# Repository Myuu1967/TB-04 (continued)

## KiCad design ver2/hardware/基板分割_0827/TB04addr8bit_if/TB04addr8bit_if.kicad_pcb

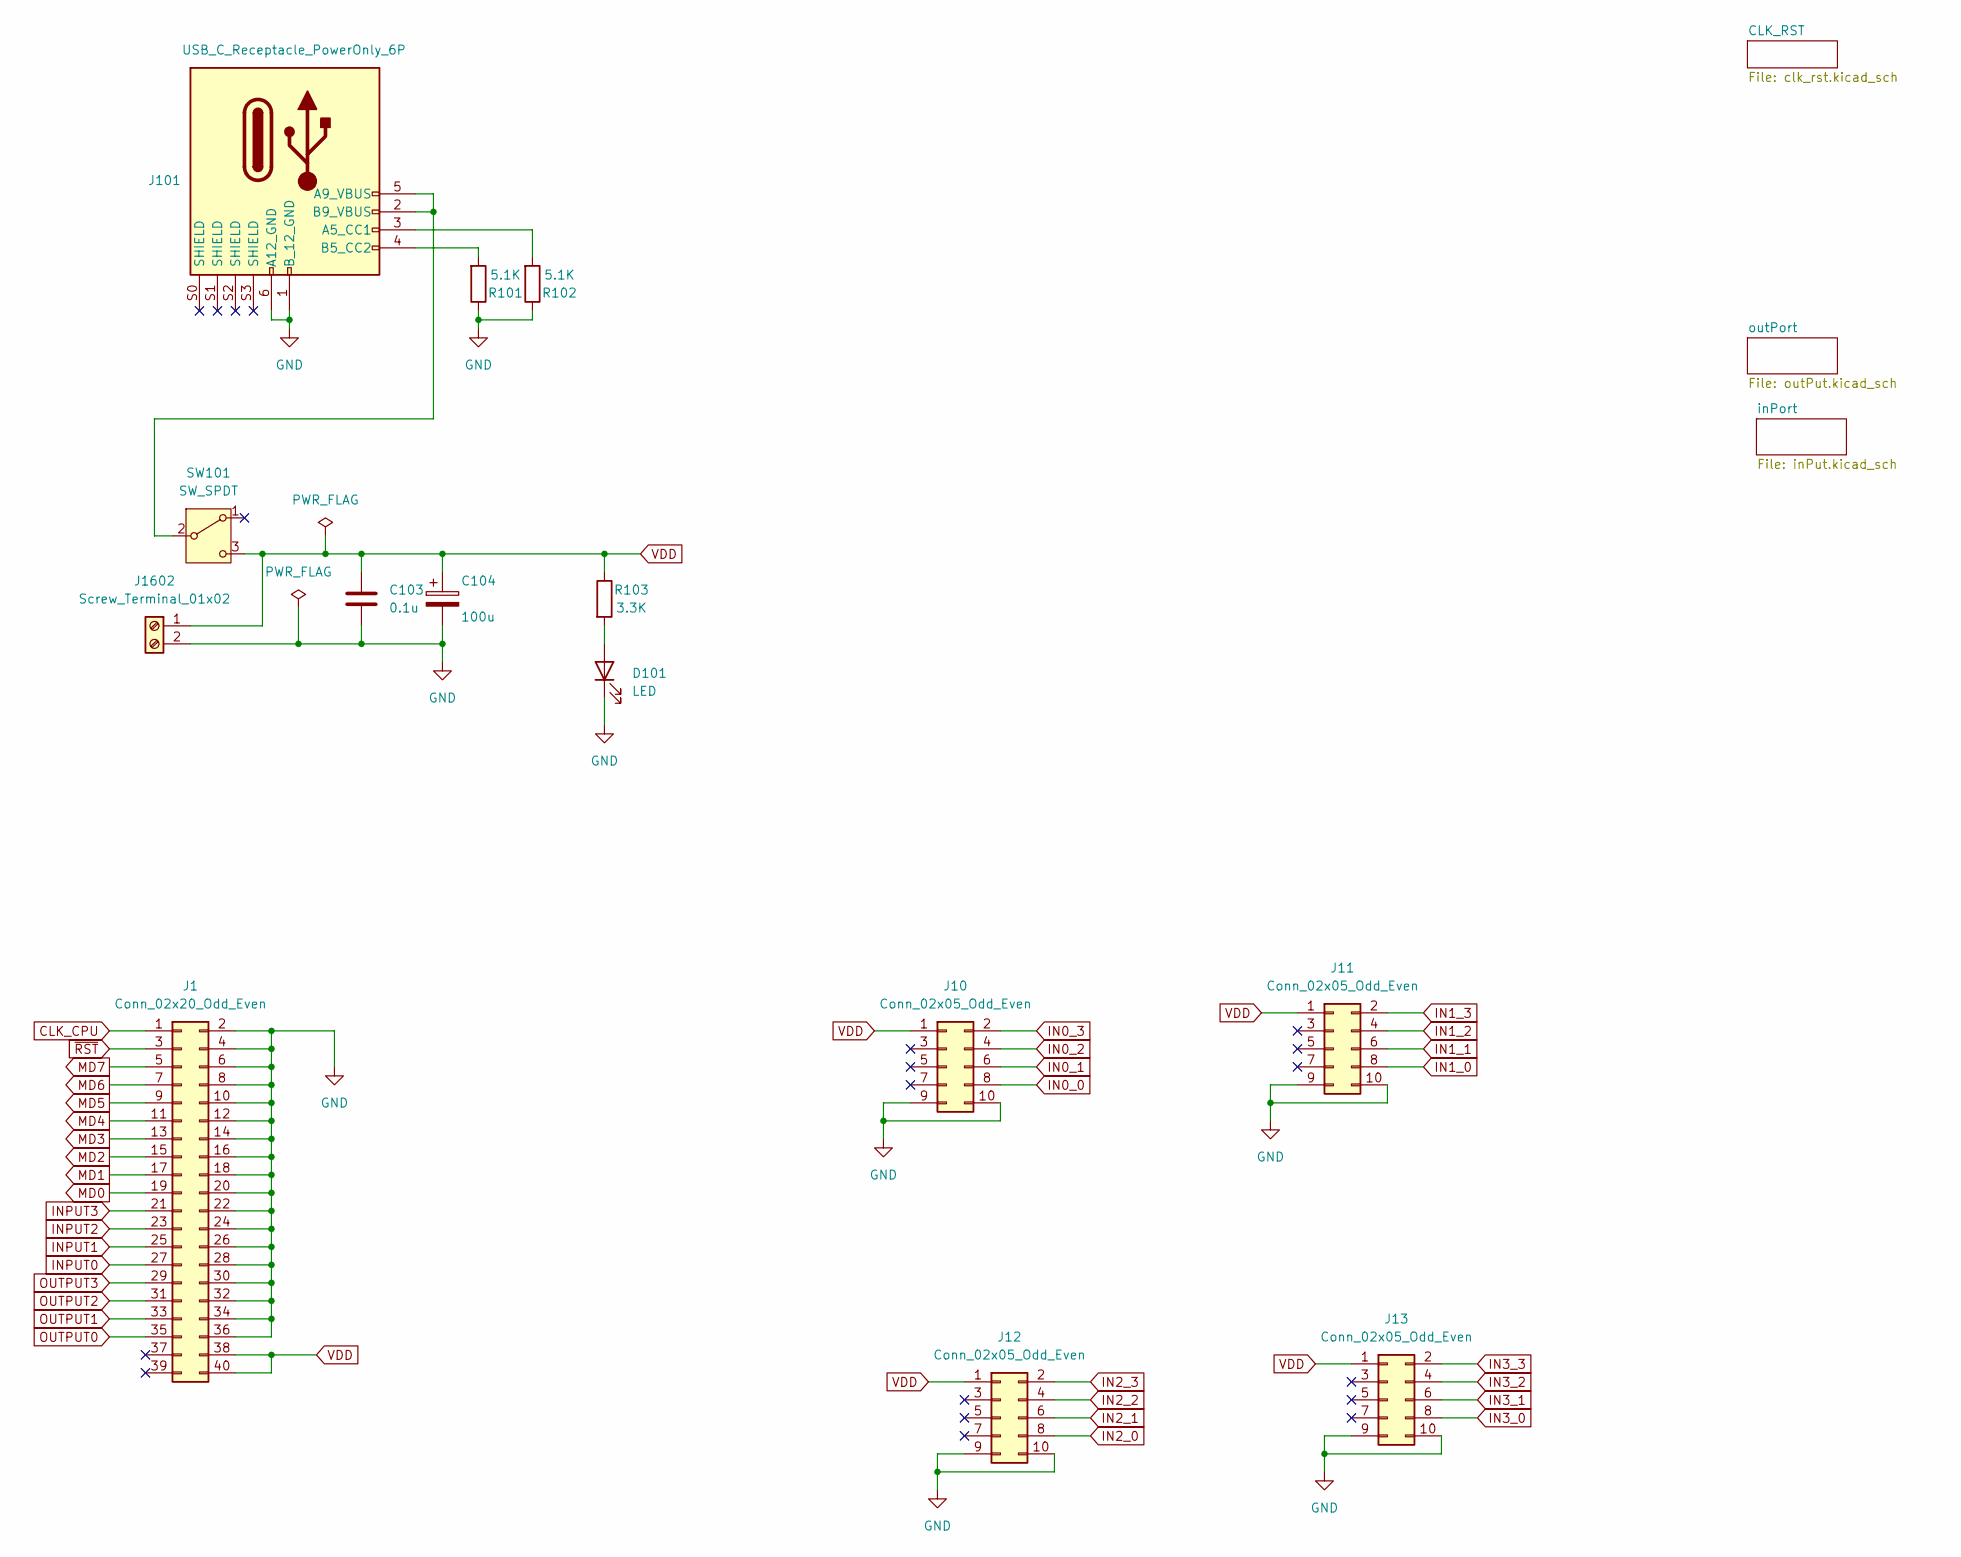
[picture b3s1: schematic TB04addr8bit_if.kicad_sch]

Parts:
C103: 0.1u; C_Disc_D4.3mm_W1.9mm_P5.00mm
C104: 100u; CP_Radial_D5.0mm_P2.00mm
D101: LED; LED_D3.0mm_Clear
J1: Conn_02x20_Odd_Even; PinSocket_2x20_P2.54mm_Vertical
J10, J11, J12, J13: Conn_02x05_Odd_Even; PinSocket_2x05_P2.54mm_Vertical
J101: USB_C_Receptacle_PowerOnly_6P; USB_C_receptacle_onlypower_tanuki
J1602: Screw_Terminal_01x02; TerminalBlock_MaiXu_MX126-5.0-02P_1x02_P5.00mm
R101, R102: 5.1K; R_Axial_DIN0207_L6.3mm_D2.5mm_P10.16mm_Horizontal
R103: 3.3K; R_Axial_DIN0207_L6.3mm_D2.5mm_P7.62mm_Horizontal
SW101: SW_SPDT; sw_slide

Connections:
CLK_CPU: J1.1; also elsewhere on the board
GND: C103.2, C104.2, D101.1 (K), J1.2, J1.4, J1.6, J1.8, J1.10, J1.12, J1.14, J1.16, J1.18, J1.20, J1.22, J1.24, J1.26, J1.28, J1.30, J1.32, J1.34, J1.36, J10.9, J10.10, J11.9, J11.10, J12.9, J12.10, J13.9, J13.10, J101.1 (B_12_GND), J101.6 (A12_GND), J1602.2, R101.1, R102.1; also elsewhere on the board
IN0_0: J10.8; also elsewhere on the board
IN0_1: J10.6; also elsewhere on the board
IN0_2: J10.4; also elsewhere on the board
IN0_3: J10.2; also elsewhere on the board
IN1_0: J11.8; also elsewhere on the board
IN1_1: J11.6; also elsewhere on the board
IN1_2: J11.4; also elsewhere on the board
IN1_3: J11.2; also elsewhere on the board
IN2_0: J12.8; also elsewhere on the board
IN2_1: J12.6; also elsewhere on the board
IN2_2: J12.4; also elsewhere on the board
IN2_3: J12.2; also elsewhere on the board
IN3_0: J13.8; also elsewhere on the board
IN3_1: J13.6; also elsewhere on the board
IN3_2: J13.4; also elsewhere on the board
IN3_3: J13.2; also elsewhere on the board
INPUT0: J1.27; also elsewhere on the board
INPUT1: J1.25; also elsewhere on the board
INPUT2: J1.23; also elsewhere on the board
INPUT3: J1.21; also elsewhere on the board
MD0: J1.19; also elsewhere on the board
MD1: J1.17; also elsewhere on the board
MD2: J1.15; also elsewhere on the board
MD3: J1.13; also elsewhere on the board
MD4: J1.11; also elsewhere on the board
MD5: J1.9; also elsewhere on the board
MD6: J1.7; also elsewhere on the board
MD7: J1.5; also elsewhere on the board
unnamed: D101.2 (A), R103.2
unnamed: J101.3 (A5_CC1), R102.2
unnamed: J101.2 (B9_VBUS), J101.5 (A9_VBUS), SW101.2 (B)
unnamed: J101.4 (B5_CC2), R101.2
OUTPUT0: J1.35; also elsewhere on the board
OUTPUT1: J1.33; also elsewhere on the board
OUTPUT2: J1.31; also elsewhere on the board
OUTPUT3: J1.29; also elsewhere on the board
VDD: C103.1, C104.1, J1.38, J1.40, J10.1, J11.1, J12.1, J13.1, J1602.1, R103.1, SW101.3 (C); also elsewhere on the board
~RST: J1.3; also elsewhere on the board

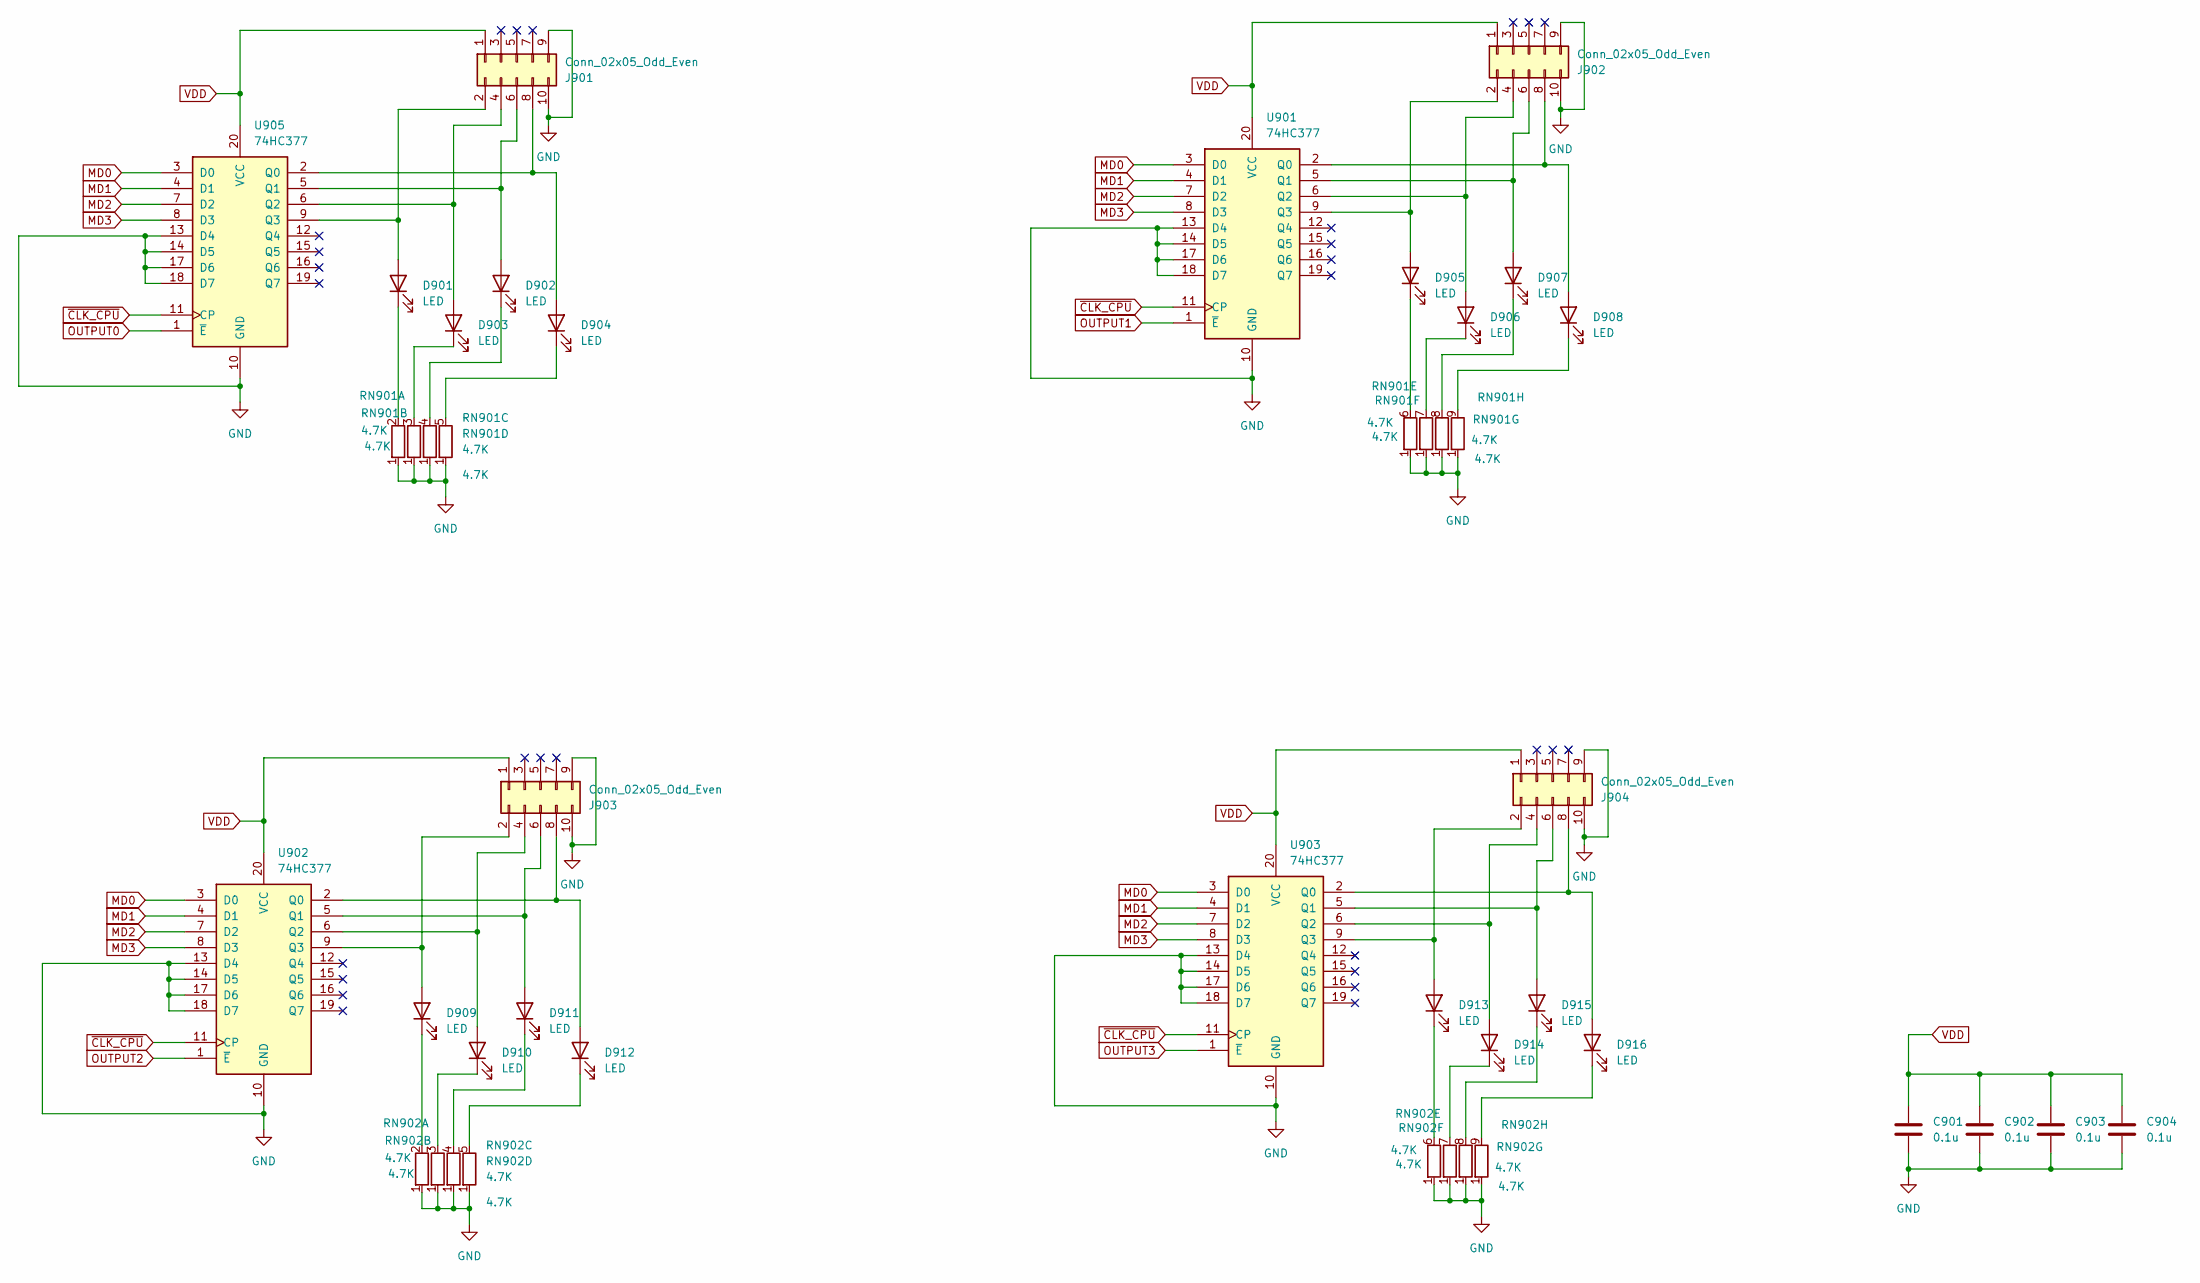
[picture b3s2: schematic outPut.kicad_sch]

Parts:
C901, C902, C903, C904: 0.1u; C_Disc_D4.3mm_W1.9mm_P5.00mm
D901, D902, D903, D904, D905, D906, D907, D908, D909, D910, D911, D912, D913, D914, D915, D916: LED; LED_D3.0mm_Clear
J901, J902, J903, J904: Conn_02x05_Odd_Even; PinSocket_2x05_P2.54mm_Vertical
RN901, RN902: 4.7K; R_Array_SIP9
U901, U902, U903, U905: 74HC377; DIP-20_W7.62mm_Socket

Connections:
GND: C901.1, C902.1, C903.1, C904.1, J901.9, J901.10, J902.9, J902.10, J903.9, J903.10, J904.9, J904.10, RN901.1 (R1), RN902.1 (R1), U901.10 (GND), U901.13 (D4), U901.14 (D5), U901.17 (D6), U901.18 (D7), U902.10 (GND), U902.13 (D4), U902.14 (D5), U902.17 (D6), U902.18 (D7), U903.10 (GND), U903.13 (D4), U903.14 (D5), U903.17 (D6), U903.18 (D7), U905.10 (GND), U905.13 (D4), U905.14 (D5), U905.17 (D6), U905.18 (D7); also elsewhere on the board
MD0: U901.3 (D0), U902.3 (D0), U903.3 (D0), U905.3 (D0); also elsewhere on the board
MD1: U901.4 (D1), U902.4 (D1), U903.4 (D1), U905.4 (D1); also elsewhere on the board
MD2: U901.7 (D2), U902.7 (D2), U903.7 (D2), U905.7 (D2); also elsewhere on the board
MD3: U901.8 (D3), U902.8 (D3), U903.8 (D3), U905.8 (D3); also elsewhere on the board
unnamed: D901.2 (A), J901.2, U905.9 (Q3)
unnamed: D901.1 (K), RN901.2 (R1.2)
unnamed: D902.2 (A), J901.6, U905.5 (Q1)
unnamed: D902.1 (K), RN901.4 (R3.2)
unnamed: D903.2 (A), J901.4, U905.6 (Q2)
unnamed: D903.1 (K), RN901.3 (R2.2)
unnamed: D904.2 (A), J901.8, U905.2 (Q0)
unnamed: D904.1 (K), RN901.5 (R4.2)
unnamed: D905.2 (A), J902.2, U901.9 (Q3)
unnamed: D905.1 (K), RN901.6 (R5.2)
unnamed: D906.2 (A), J902.4, U901.6 (Q2)
unnamed: D906.1 (K), RN901.7 (R6.2)
unnamed: D907.2 (A), J902.6, U901.5 (Q1)
unnamed: D907.1 (K), RN901.8 (R7.2)
unnamed: D908.2 (A), J902.8, U901.2 (Q0)
unnamed: D908.1 (K), RN901.9 (R8.2)
unnamed: D909.2 (A), J903.2, U902.9 (Q3)
unnamed: D909.1 (K), RN902.2 (R1.2)
unnamed: D910.2 (A), J903.4, U902.6 (Q2)
unnamed: D910.1 (K), RN902.3 (R2.2)
unnamed: D911.2 (A), J903.6, U902.5 (Q1)
unnamed: D911.1 (K), RN902.4 (R3.2)
unnamed: D912.2 (A), J903.8, U902.2 (Q0)
unnamed: D912.1 (K), RN902.5 (R4.2)
unnamed: D913.2 (A), J904.2, U903.9 (Q3)
unnamed: D913.1 (K), RN902.6 (R5.2)
unnamed: D914.2 (A), J904.4, U903.6 (Q2)
unnamed: D914.1 (K), RN902.7 (R6.2)
unnamed: D915.2 (A), J904.6, U903.5 (Q1)
unnamed: D915.1 (K), RN902.8 (R7.2)
unnamed: D916.2 (A), J904.8, U903.2 (Q0)
unnamed: D916.1 (K), RN902.9 (R8.2)
OUTPUT0: U905.1 (~E); also elsewhere on the board
OUTPUT1: U901.1 (~E); also elsewhere on the board
OUTPUT2: U902.1 (~E); also elsewhere on the board
OUTPUT3: U903.1 (~E); also elsewhere on the board
VDD: C901.2, C902.2, C903.2, C904.2, J901.1, J902.1, J903.1, J904.1, U901.20 (VCC), U902.20 (VCC), U903.20 (VCC), U905.20 (VCC); also elsewhere on the board
~CLK_CPU: U901.11 (CP), U902.11 (CP), U903.11 (CP), U905.11 (CP); also elsewhere on the board

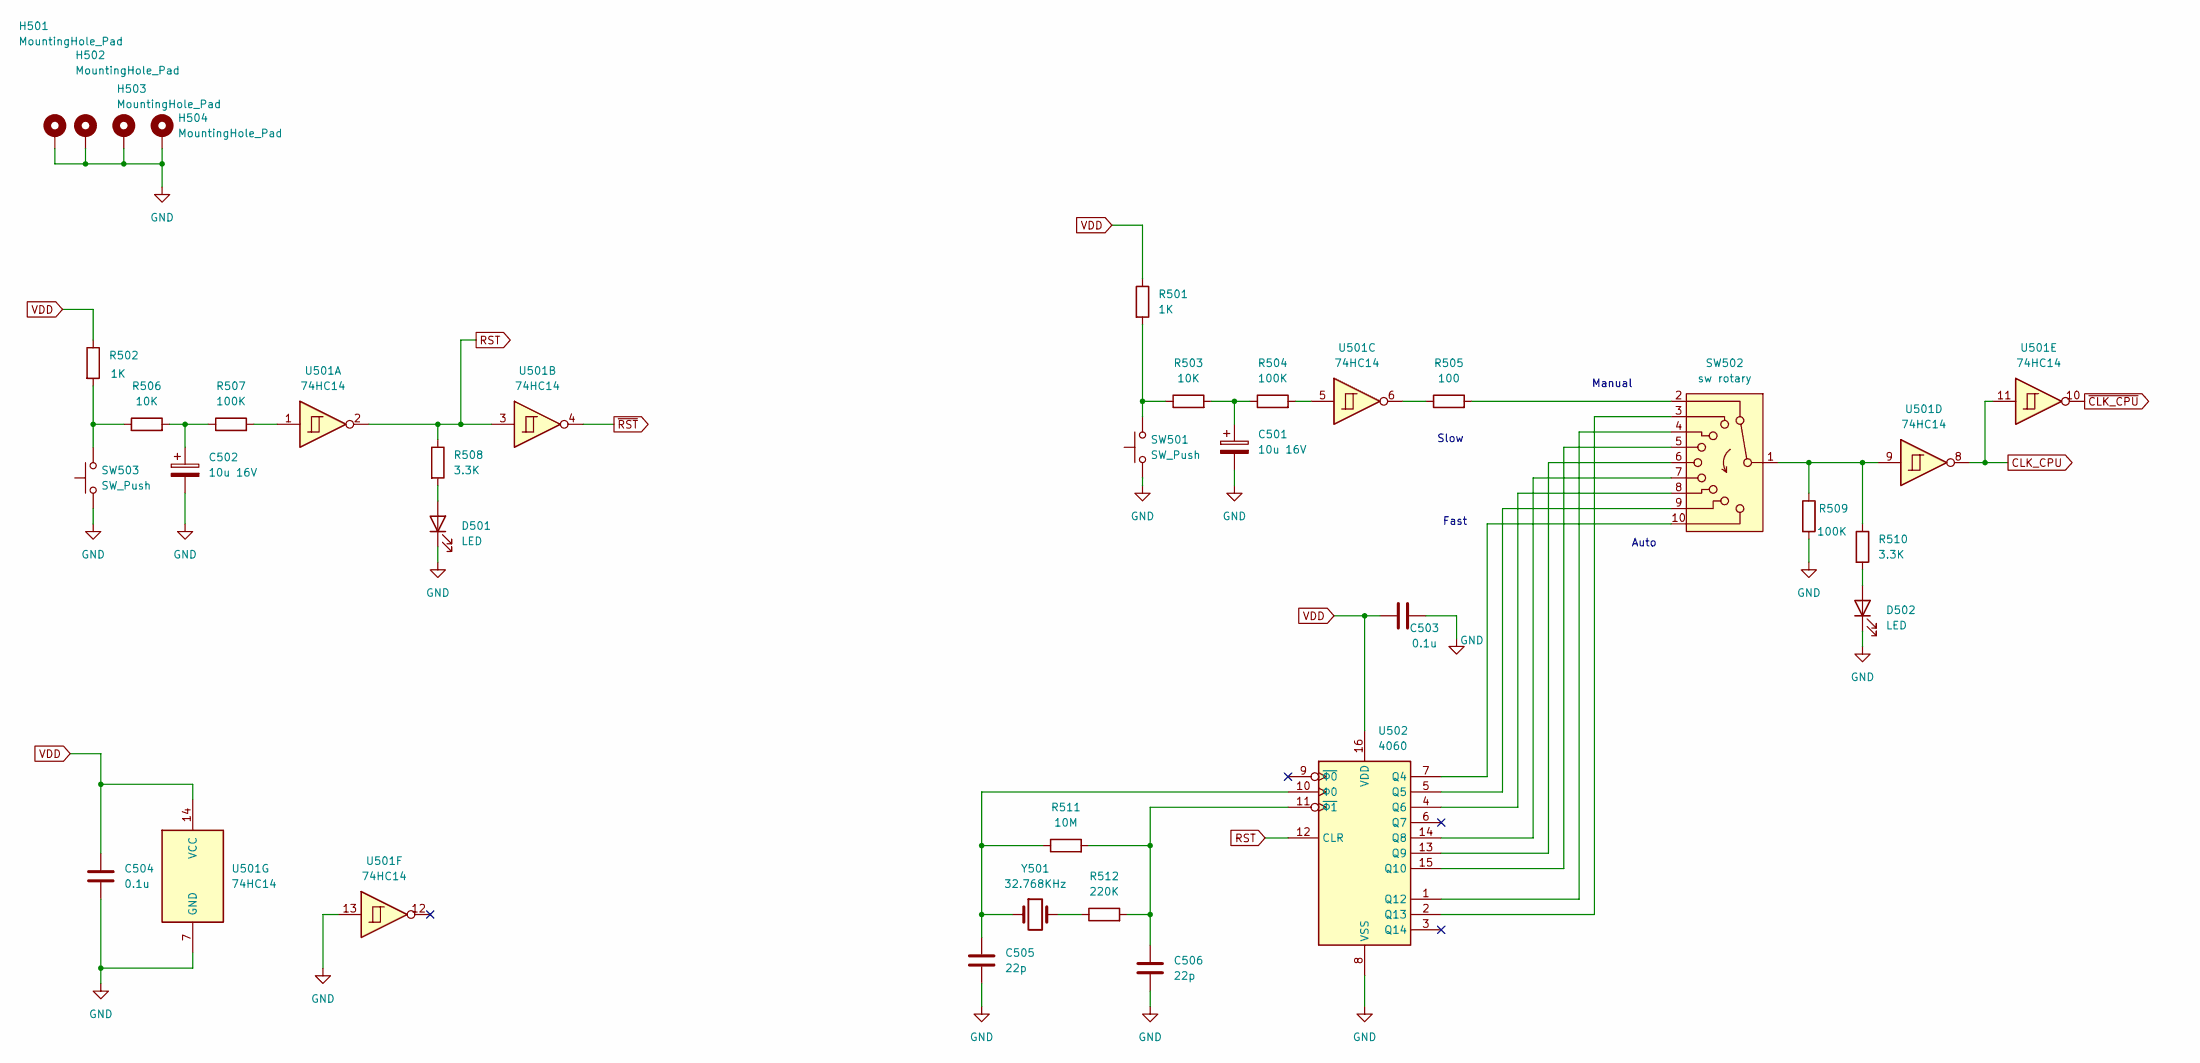
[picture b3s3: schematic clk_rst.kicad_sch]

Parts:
C501, C502: 10u 16V; CP_Radial_D5.0mm_P2.00mm
C503, C504: 0.1u; C_Disc_D4.3mm_W1.9mm_P5.00mm
C505, C506: 22p; C_Disc_D4.3mm_W1.9mm_P5.00mm
D501, D502: LED; LED_D3.0mm_Clear
H501, H502, H503, H504: MountingHole_Pad; MountingHole_3.2mm_M3_Pad_Via
R501, R502: 1K; R_Axial_DIN0207_L6.3mm_D2.5mm_P10.16mm_Horizontal
R503, R506: 10K; R_Axial_DIN0207_L6.3mm_D2.5mm_P10.16mm_Horizontal
R504, R507, R509: 100K; R_Axial_DIN0207_L6.3mm_D2.5mm_P7.62mm_Horizontal
R505: 100; R_Axial_DIN0207_L6.3mm_D2.5mm_P10.16mm_Horizontal
R508, R510: 3.3K; R_Axial_DIN0207_L6.3mm_D2.5mm_P7.62mm_Horizontal
R511: 10M; R_Axial_DIN0207_L6.3mm_D2.5mm_P10.16mm_Horizontal
R512: 220K; R_Axial_DIN0207_L6.3mm_D2.5mm_P10.16mm_Horizontal
SW501, SW503: SW_Push; SW_Tactile_Straight_KSL0Axx1LFTR
SW502: sw rotary; SW_Rotary_1x9_Alpha_SR1712F-0109
U501: 74HC14; DIP-14_W7.62mm_Socket
U502: 4060; DIP-16_W7.62mm_Socket
Y501: 32.768KHz; PinSocket_1x02_P2.00mm_Vertical

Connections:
CLK_CPU: U501.8, U501.11; also elsewhere on the board
GND: C501.2, C502.2, C503.1, C504.2, C505.2, C506.2, D501.1 (K), D502.1 (K), H501.1 (1_1), H502.1 (1_1), H503.1 (1_1), H504.1 (1_1), R509.2, SW501.1, SW503.1, U501.7 (GND), U501.13, U502.8 (VSS); also elsewhere on the board
unnamed: C501.1, R503.2, R504.1
unnamed: C502.1, R506.2, R507.1
unnamed: D501.2 (A), R508.2
unnamed: D502.2 (A), R510.2
unnamed: R501.2, R503.1, SW501.2
unnamed: R502.2, R506.1, SW503.2
unnamed: R504.2, U501.5
unnamed: R505.1, U501.6
unnamed: R505.2, SW502.2
unnamed: R507.2, U501.1
unnamed: R509.1, R510.1, SW502.1, U501.9
unnamed: R512.1, Y501.2
unnamed: SW502.10, U502.7 (Q4)
unnamed: SW502.9, U502.5 (Q5)
unnamed: SW502.8, U502.4 (Q6)
unnamed: SW502.7, U502.14 (Q8)
unnamed: SW502.6, U502.13 (Q9)
unnamed: SW502.5, U502.15 (Q10)
unnamed: SW502.4, U502.1 (Q12)
unnamed: SW502.3, U502.2 (Q13)
unnamed: C506.1, R511.2, R512.2, U502.11 (~Φ1)
unnamed: C505.1, R511.1, U502.10 (Φ0), Y501.1
RST: R508.1, U501.2, U501.3, U502.12 (CLR)
VDD: C503.2, C504.1, R501.1, R502.1, U501.14 (VCC), U502.16 (VDD); also elsewhere on the board
~CLK_CPU: U501.10; also elsewhere on the board
~RST: U501.4; also elsewhere on the board

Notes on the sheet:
Auto
Manual
Slow
Fast

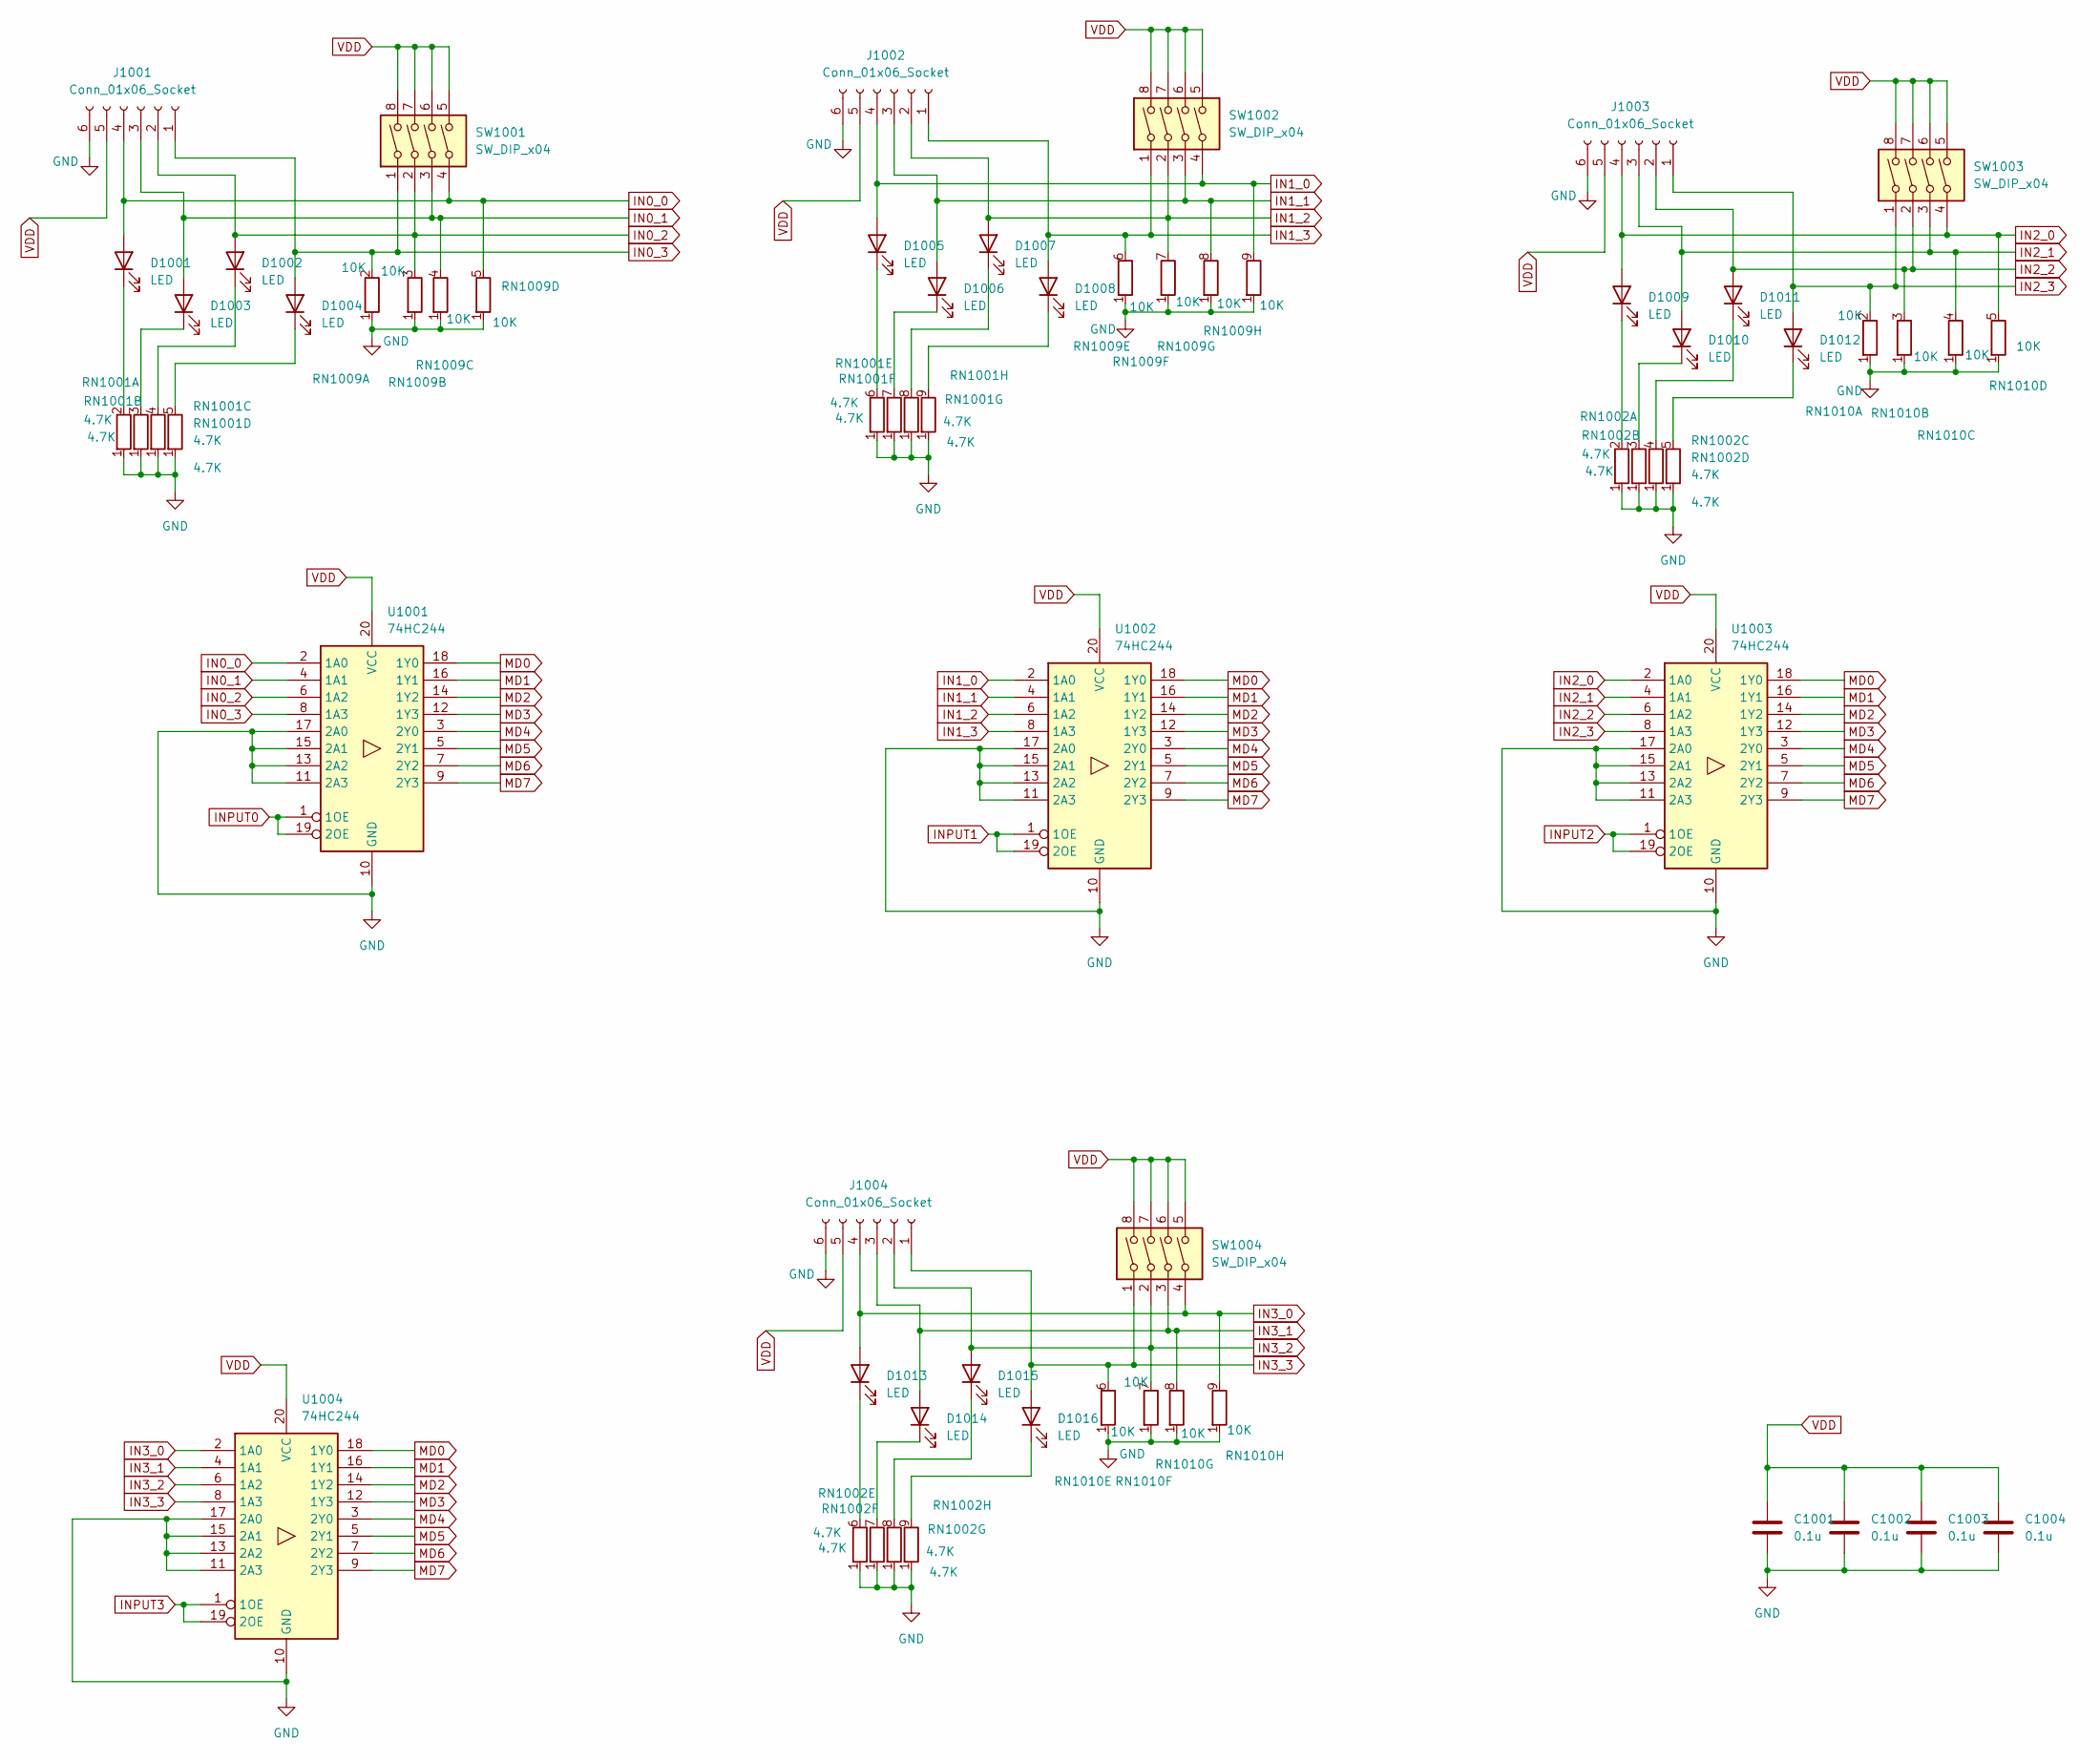
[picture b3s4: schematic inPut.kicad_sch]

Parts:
C1001, C1002, C1003, C1004: 0.1u; C_Disc_D4.3mm_W1.9mm_P5.00mm
D1001, D1002, D1003, D1004, D1005, D1006, D1007, D1008, D1009, D1010, D1011, D1012, D1013, D1014, D1015, D1016: LED; LED_D3.0mm_Clear
J1001, J1002, J1003, J1004: Conn_01x06_Socket; PinSocket_1x06_P2.54mm_Vertical
RN1001, RN1002: 4.7K; R_Array_SIP9
RN1009, RN1010: 10K; R_Array_SIP9
SW1001, SW1002, SW1003, SW1004: SW_DIP_x04; SW_DIP_SPSTx04_Slide_9.78x12.34mm_W7.62mm_P2.54mm
U1001, U1002, U1003, U1004: 74HC244; DIP-20_W7.62mm_Socket

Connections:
GND: C1001.1, C1002.1, C1003.1, C1004.1, J1001.6, J1002.6, J1003.6, J1004.6, RN1001.1 (R1), RN1002.1 (R1), RN1009.1 (R1), RN1010.1 (R1), U1001.10 (GND), U1001.11 (2A3), U1001.13 (2A2), U1001.15 (2A1), U1001.17 (2A0), U1002.10 (GND), U1002.11 (2A3), U1002.13 (2A2), U1002.15 (2A1), U1002.17 (2A0), U1003.10 (GND), U1003.11 (2A3), U1003.13 (2A2), U1003.15 (2A1), U1003.17 (2A0), U1004.10 (GND), U1004.11 (2A3), U1004.13 (2A2), U1004.15 (2A1), U1004.17 (2A0); also elsewhere on the board
IN0_0: D1001.2 (A), J1001.4, RN1009.5 (R4.2), SW1001.4, U1001.2 (1A0); also elsewhere on the board
IN0_1: D1003.2 (A), J1001.3, RN1009.4 (R3.2), SW1001.3, U1001.4 (1A1); also elsewhere on the board
IN0_2: D1002.2 (A), J1001.2, RN1009.3 (R2.2), SW1001.2, U1001.6 (1A2); also elsewhere on the board
IN0_3: D1004.2 (A), J1001.1, RN1009.2 (R1.2), SW1001.1, U1001.8 (1A3); also elsewhere on the board
IN1_0: D1005.2 (A), J1002.4, RN1009.9 (R8.2), SW1002.4, U1002.2 (1A0); also elsewhere on the board
IN1_1: D1006.2 (A), J1002.3, RN1009.8 (R7.2), SW1002.3, U1002.4 (1A1); also elsewhere on the board
IN1_2: D1007.2 (A), J1002.2, RN1009.7 (R6.2), SW1002.2, U1002.6 (1A2); also elsewhere on the board
IN1_3: D1008.2 (A), J1002.1, RN1009.6 (R5.2), SW1002.1, U1002.8 (1A3); also elsewhere on the board
IN2_0: D1009.2 (A), J1003.4, RN1010.5 (R4.2), SW1003.4, U1003.2 (1A0); also elsewhere on the board
IN2_1: D1010.2 (A), J1003.3, RN1010.4 (R3.2), SW1003.3, U1003.4 (1A1); also elsewhere on the board
IN2_2: D1011.2 (A), J1003.2, RN1010.3 (R2.2), SW1003.2, U1003.6 (1A2); also elsewhere on the board
IN2_3: D1012.2 (A), J1003.1, RN1010.2 (R1.2), SW1003.1, U1003.8 (1A3); also elsewhere on the board
IN3_0: D1013.2 (A), J1004.4, RN1010.9 (R8.2), SW1004.4, U1004.2 (1A0); also elsewhere on the board
IN3_1: D1014.2 (A), J1004.3, RN1010.8 (R7.2), SW1004.3, U1004.4 (1A1); also elsewhere on the board
IN3_2: D1015.2 (A), J1004.2, RN1010.7 (R6.2), SW1004.2, U1004.6 (1A2); also elsewhere on the board
IN3_3: D1016.2 (A), J1004.1, RN1010.6 (R5.2), SW1004.1, U1004.8 (1A3); also elsewhere on the board
INPUT0: U1001.1 (1OE), U1001.19 (2OE); also elsewhere on the board
INPUT1: U1002.1 (1OE), U1002.19 (2OE); also elsewhere on the board
INPUT2: U1003.1 (1OE), U1003.19 (2OE); also elsewhere on the board
INPUT3: U1004.1 (1OE), U1004.19 (2OE); also elsewhere on the board
MD0: U1001.18 (1Y0), U1002.18 (1Y0), U1003.18 (1Y0), U1004.18 (1Y0); also elsewhere on the board
MD1: U1001.16 (1Y1), U1002.16 (1Y1), U1003.16 (1Y1), U1004.16 (1Y1); also elsewhere on the board
MD2: U1001.14 (1Y2), U1002.14 (1Y2), U1003.14 (1Y2), U1004.14 (1Y2); also elsewhere on the board
MD3: U1001.12 (1Y3), U1002.12 (1Y3), U1003.12 (1Y3), U1004.12 (1Y3); also elsewhere on the board
MD4: U1001.3 (2Y0), U1002.3 (2Y0), U1003.3 (2Y0), U1004.3 (2Y0); also elsewhere on the board
MD5: U1001.5 (2Y1), U1002.5 (2Y1), U1003.5 (2Y1), U1004.5 (2Y1); also elsewhere on the board
MD6: U1001.7 (2Y2), U1002.7 (2Y2), U1003.7 (2Y2), U1004.7 (2Y2); also elsewhere on the board
MD7: U1001.9 (2Y3), U1002.9 (2Y3), U1003.9 (2Y3), U1004.9 (2Y3); also elsewhere on the board
unnamed: D1001.1 (K), RN1001.2 (R1.2)
unnamed: D1002.1 (K), RN1001.4 (R3.2)
unnamed: D1003.1 (K), RN1001.3 (R2.2)
unnamed: D1004.1 (K), RN1001.5 (R4.2)
unnamed: D1005.1 (K), RN1001.6 (R5.2)
unnamed: D1006.1 (K), RN1001.7 (R6.2)
unnamed: D1007.1 (K), RN1001.8 (R7.2)
unnamed: D1008.1 (K), RN1001.9 (R8.2)
unnamed: D1009.1 (K), RN1002.2 (R1.2)
unnamed: D1010.1 (K), RN1002.3 (R2.2)
unnamed: D1011.1 (K), RN1002.4 (R3.2)
unnamed: D1012.1 (K), RN1002.5 (R4.2)
unnamed: D1013.1 (K), RN1002.6 (R5.2)
unnamed: D1014.1 (K), RN1002.7 (R6.2)
unnamed: D1015.1 (K), RN1002.8 (R7.2)
unnamed: D1016.1 (K), RN1002.9 (R8.2)
VDD: C1001.2, C1002.2, C1003.2, C1004.2, J1001.5, J1002.5, J1003.5, J1004.5, SW1001.5, SW1001.6, SW1001.7, SW1001.8, SW1002.5, SW1002.6, SW1002.7, SW1002.8, SW1003.5, SW1003.6, SW1003.7, SW1003.8, SW1004.5, SW1004.6, SW1004.7, SW1004.8, U1001.20 (VCC), U1002.20 (VCC), U1003.20 (VCC), U1004.20 (VCC); also elsewhere on the board

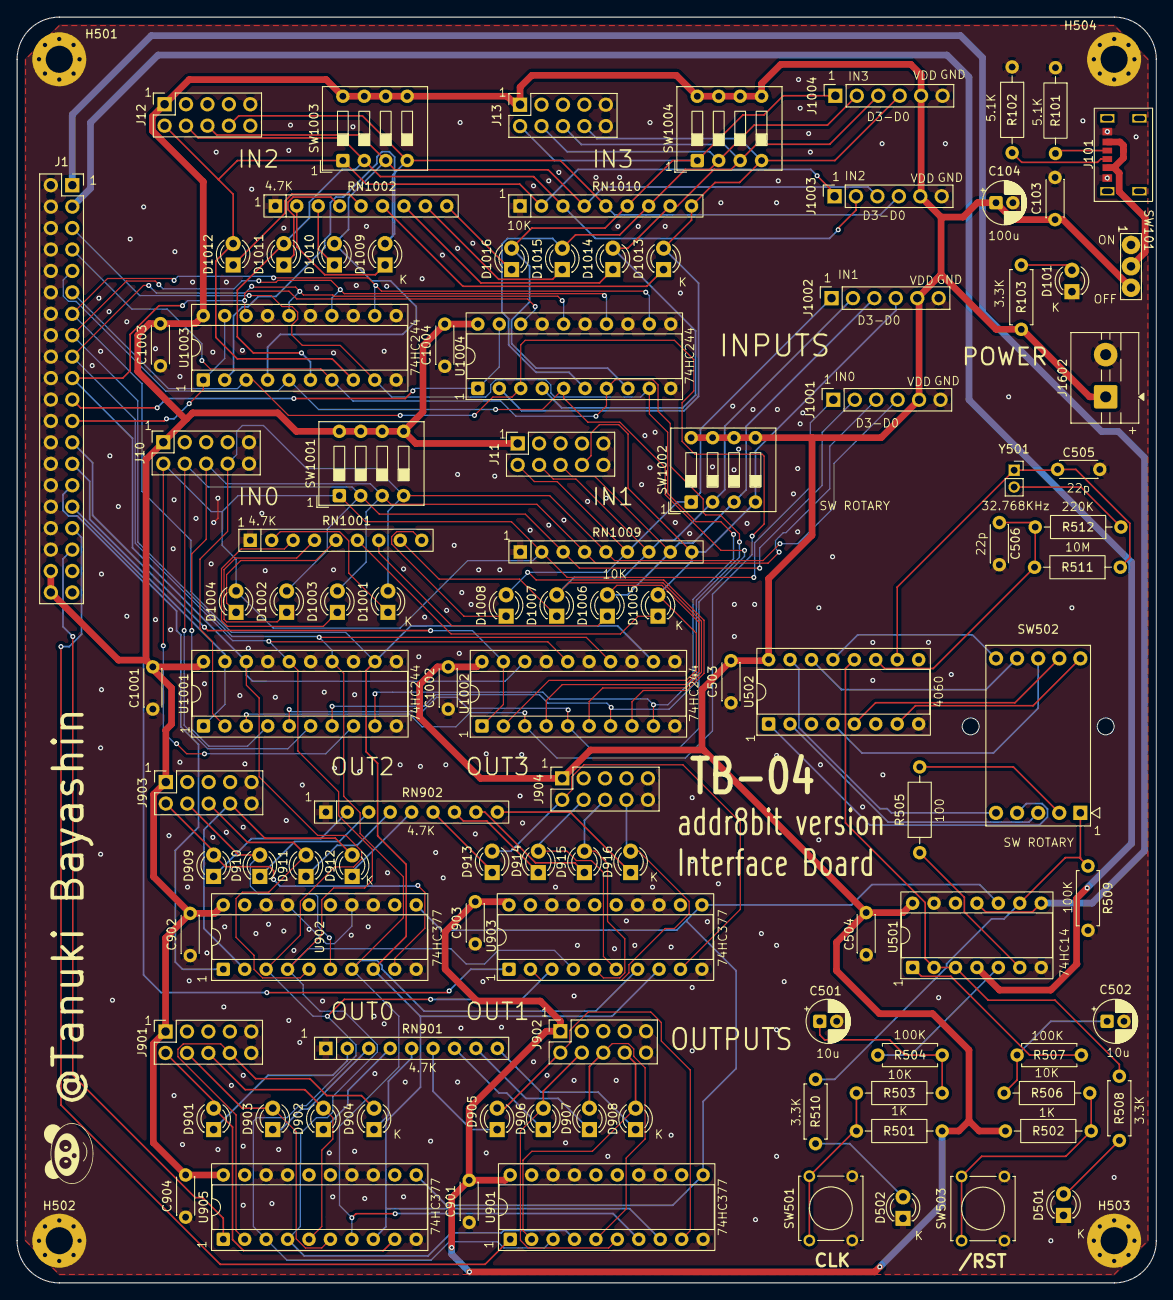
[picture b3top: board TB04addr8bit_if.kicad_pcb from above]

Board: 2 copper layers, 135.0 x 150.0 mm, 110 parts (0 on the bottom side), 112 nets.
